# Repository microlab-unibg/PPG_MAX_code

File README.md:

# IoT_Sensor

This GitHub project contains a library for configuring registers and reading data from the MAX86916 sensor to calculate heart rate (HR) using a peak detection algorithm. The MAX86916 is a highly integrated optical sensor module that can be used for pulse oximetry and heart rate monitoring. The library provided in this project simplifies the process of interfacing with the sensor and extracting the HR information using an efficient peak detection algorithm. The library can be easily integrated into an existing codebase, and the project also includes sample code to demonstrate the usage of the library.

## HR-Calculation

### Begin()
- Starts I2C communication between Arduino and sensor by calling the Wire.begin() function.
- Sets the clock speed for the I2C communication to I2C_SPEED_FAST using the Wire.setClock() function.
- Calls the read_Part_ID() function to read the part ID from the MAX86916 sensor.
- Compares the part ID read from the sensor to the expected part ID (MAX86916_EXPECTED_PART_ID).
- If the part ID does not match the expected part ID, the function returns false, indicating an error.
- Calls the read_Revision_ID() function to read the revision ID from the MAX86916 sensor.
- If everything is working correctly, the function returns true.
### Setup()
- Calls the softReset() function to reset the sensor.
- Configures the FIFO (First In First Out) buffer by calling the setFIFOAverage() function to set the sample average, and the enableFIFORollover() function to allow the FIFO to roll over.
- Configures the LED mode by calling the setLEDMode() function with the specified ledMode parameter. The activeLEDs variable is set based on the ledMode parameter.
- Configures the particle sensing by calling the setADCRange(), setSampleRate(), and setPulseWidth() functions with the specified parameters.
- Configures the LED pulse amplitude by calling the setAllLEDRange() function with the specified range parameter, and the setPA_IR(), setPA_RED(), setPA_GREEN(), setPA_BLUE(), and setPA_PROX() functions with the specified powerLevel parameter.
- Configures the Flex-LED mode by calling the enableSlot() function to enable the reading of the LEDs, depending on the ledMode parameter.
- Calls the clearFIFO() function to reset the FIFO buffer.
### Read FIFO()
- The function returns a 16-bit unsigned integer that represents the number of new data samples that were read from the sensor.
- The function first reads the read and write pointers of the FIFO register to determine how much new data is available.
- If there is new data available, the function calculates the number of samples to read and the number of bytes to request from the sensor.
- The function then enters a loop where it repeatedly requests blocks of data from the sensor and stores the data in the buffer.
- Within the loop, the function reads three bytes at a time and converts them to 32-bit unsigned integers.
- The function then applies a bit mask to zero out all but the 18 least significant bits of the integer, which are the meaningful data bits.
- Finally, the function stores the converted integer values in the appropriate arrays within the buffer.
### Get Current value()
This function is a method of a MAX86916 class that retrieves the most recent Green value from the sensor data buffer. It first calls the safeCheck() function, which checks the sensor for new data for 250ms and returns a boolean indicating whether new data was found. If new data is found, it returns the most recent Green value from the sensor_data_buffer array by accessing the array element at the current head index. If no new data is found, it returns 0 to indicate that the sensor failed to find new data. This function assumes that the sensor data buffer has been properly initialized and that the head index has been properly updated by the readFIFO() function.
### Apply lowpassfilter()
This function applies a first-order low-pass filter to the input signal using the one-pole recursive filter algorithm. The filter is implemented using a lowpassFilter1p struct that contains the previous input value and the filter coefficient (pt1K).
The function then updates the previous input value to the current output value for the next iteration of the filter.
Finally, the function returns the filtered output signal.
### Apply removeDC()
This function applies a DC removal filter to the input signal using a first-order high-pass filter with the given alpha coefficient. The function takes three parameters: the input signal to be filtered (x), the previous filtered value (prev_w), and the alpha coefficient (alpha) that determines the amount of filtering.
The function creates a DigitalFilter::dcFilter_t struct to hold the filtered and intermediate values, and returns the filtered value at the end.
### Apply medianfilter()
This function applies a mean difference filter to the input signal using a sliding window of a specified size. The function takes two parameters: the input signal to be filtered (M), and a pointer to the meanDiffFilter_t struct (filterValues) containing the filter parameters.
The function calculates the filtered output signal as the difference between the input signal and the moving average of the window. The filter parameters include an array of values (values), the sum of the values (sum), the index of the current position in the sliding window (index), and the count of values in the sliding window (count).
The function first subtracts the oldest value in the sliding window from the sum. It then inserts the new value at the current index and adds it to the sum. The index is then moved to the next position in the sliding window. If the sliding window is not full, the count of values in the window is increased.
The function calculates the moving average of the window by dividing the sum by the count. It then returns the difference between the moving average and the input signal.
### Apply butterworthfilter()
This function applies a fourth-order low-pass filter to the input signal using pre-calculated filter coefficients. The coefficients were calculated in Matlab based on some samples of the input signal.
The filter has four zeros (NZEROS) and four poles (NPOLES), and a gain factor (GAIN) of 3.775352055e+02.
The function uses two arrays, xv and yv, to maintain a history of the input and output values, respectively. The input value x is first scaled by the pre-calculated gain and then inserted into the input history buffer.
The output history buffer is shifted, and the new output value is calculated using the pre-calculated filter coefficients and the history buffer values. The function returns the new output value.
Note that the filter coefficients and the gain factor were pre-calculated in Matlab and are hardcoded in the function.
### Peak detection algorithm
After the signal was filtered, the next step was to apply the peak detection algorithm to the filtered signal. This algorithm identified the peaks in the signal, which corresponded to the heartbeats.
### Calculate HR
For each peak found, the time between the different peaks was calculated to determine the heart rate

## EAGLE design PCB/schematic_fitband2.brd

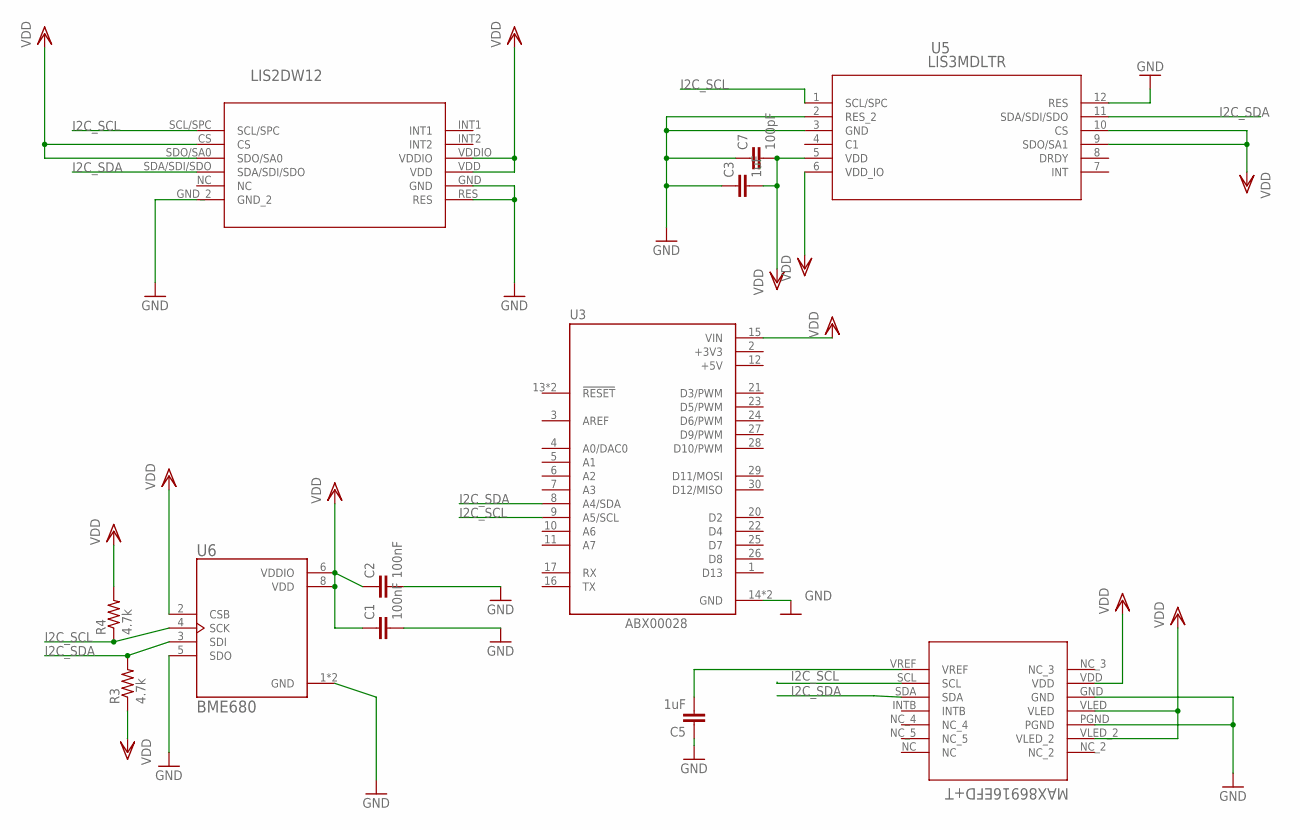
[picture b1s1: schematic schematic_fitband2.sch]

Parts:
C1, C2: 100nF; 221E_PASSIVES_C0402
C3, C5: 1uF; 221E_PASSIVES_C0402
C7: 100pF; 221E_PASSIVES_C0402
R3, R4: 4.7k; M0805
U1: MAX86916EFD+T; 21-100325_90-100122
U2: LIS2DW12; LIS2DW12_LGA-12_2X2X0P7_STM
U3: ABX00028; MODULE_ABX00028
U5: LIS3MDLTR; LGA-12_2X2X1_STM
U6: BME680; PSON80P300X300X100-8N

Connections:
+3V3: U3.2 (+3V3)
+5V: U3.12 (+5V)
GND: C1.P$2 (2), C2.P$2 (2), C3.P$1 (1), C5.P$1 (1), C7.P$1 (1), U1.GND, U1.PGND, U2.GND, U2.GND_2, U2.RES, U3.14 (GND), U3.19 (GND), U5.2 (RES_2), U5.3 (GND), U5.12 (RES), U6.1 (GND), U6.5 (SDO), U6.7 (GND)
I2C_SCL: R4.1, U1.SCL, U2.SCL/SPC, U3.9 (A5/SCL), U5.1 (SCL/SPC), U6.4 (SCK)
I2C_SDA: R3.2, U1.SDA, U2.SDA/SDI/SDO, U3.8 (A4/SDA), U5.11 (SDA/SDI/SDO), U6.3 (SDI)
unnamed: C5.P$2 (2), U1.VREF
VDD: C1.P$1 (1), C2.P$1 (1), C3.P$2 (2), C7.P$2 (2), R3.1, R4.2, U1.VDD, U1.VLED, U1.VLED_2, U2.CS, U2.SDO/SA0, U2.VDD, U2.VDDIO, U3.15 (VIN), U5.5 (VDD), U5.6 (VDD_IO), U5.9 (SDO/SA1), U5.10 (CS), U6.2 (CSB), U6.6 (VDDIO), U6.8 (VDD)

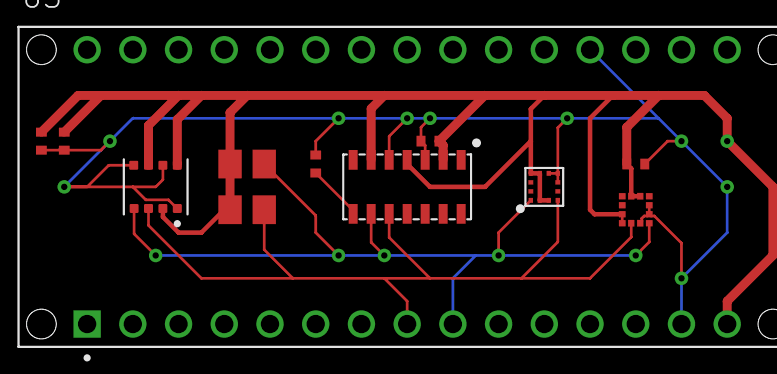
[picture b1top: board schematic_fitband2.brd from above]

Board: 2 copper layers, 12 parts (0 on the bottom side), 5 nets.

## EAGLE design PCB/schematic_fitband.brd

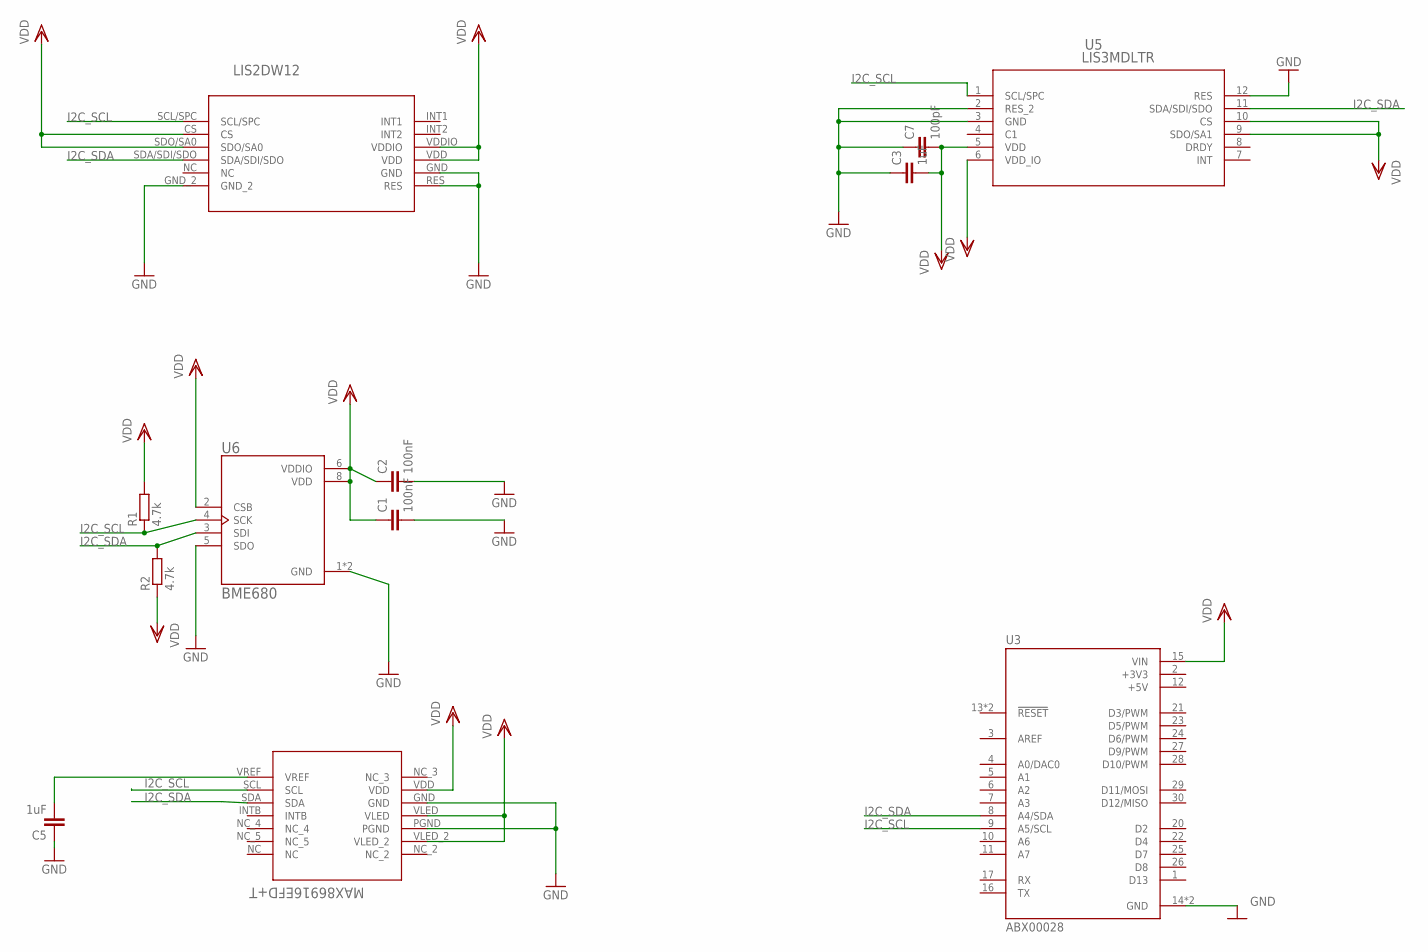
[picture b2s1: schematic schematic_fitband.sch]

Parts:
C1, C2: 100nF; 221E_PASSIVES_C0402
C3, C5: 1uF; 221E_PASSIVES_C0402
C7: 100pF; 221E_PASSIVES_C0402
R1, R2: 4.7k; MINI_MELF-0204R
U1: MAX86916EFD+T; 21-100325_90-100122
U2: LIS2DW12; LIS2DW12_LGA-12_2X2X0P7_STM
U3: ABX00028; MODULE_ABX00028
U5: LIS3MDLTR; LGA-12_2X2X1_STM
U6: BME680; PSON80P300X300X100-8N

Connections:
+3V3: U3.2 (+3V3)
+5V: U3.12 (+5V)
GND: C1.P$2 (2), C2.P$2 (2), C3.P$1 (1), C5.P$1 (1), C7.P$1 (1), U1.GND, U1.PGND, U2.GND, U2.GND_2, U2.RES, U3.14 (GND), U3.19 (GND), U5.2 (RES_2), U5.3 (GND), U5.12 (RES), U6.1 (GND), U6.5 (SDO), U6.7 (GND)
I2C_SCL: R1.1, U1.SCL, U2.SCL/SPC, U3.9 (A5/SCL), U5.1 (SCL/SPC), U6.4 (SCK)
I2C_SDA: R2.2, U1.SDA, U2.SDA/SDI/SDO, U3.8 (A4/SDA), U5.11 (SDA/SDI/SDO), U6.3 (SDI)
unnamed: C5.P$2 (2), U1.VREF
unnamed: R1.2, U6.2 (CSB)
VDD: C1.P$1 (1), C2.P$1 (1), C3.P$2 (2), C7.P$2 (2), R2.1, U1.VDD, U1.VLED, U1.VLED_2, U2.CS, U2.SDO/SA0, U2.VDD, U2.VDDIO, U3.15 (VIN), U5.5 (VDD), U5.6 (VDD_IO), U5.9 (SDO/SA1), U5.10 (CS), U6.6 (VDDIO), U6.8 (VDD)

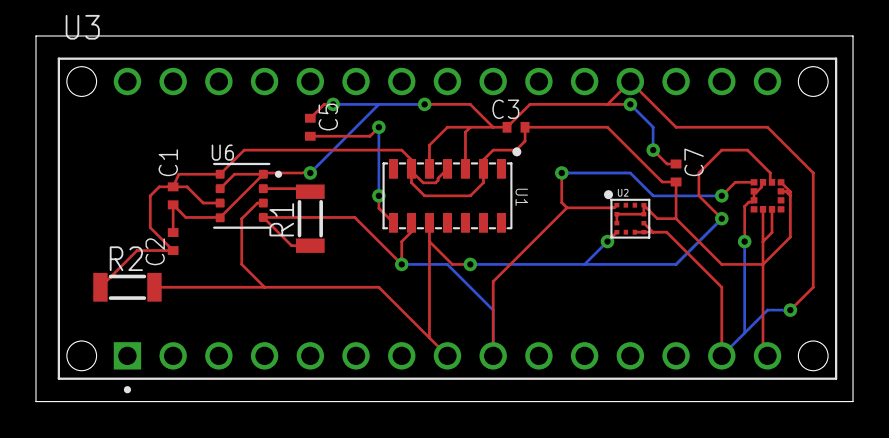
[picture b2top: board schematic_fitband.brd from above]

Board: 2 copper layers, 45.4 x 20.3 mm, 12 parts (0 on the bottom side), 6 nets.

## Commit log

2023-02-10 Configuration classes
2023-02-13 PPG configuration
2023-02-13 led_current configuration
2023-02-20 led_sequence configuration+ fifo configuration
2023-02-21 small changes
2023-03-12 MAX8691 class
2023-03-13 Create Use
2023-04-16 project structure
2023-04-18 electronics
2023-12-18 FIX - Missing declarations in cmFilter.cpp and file structure
2023-12-20 FIX - GAIN didnt have space godd****

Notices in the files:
parts and their libraries:
COPYRIGHT: Copyright (C) 2018 Accelerated Designs. All rights reserved
COPYRIGHT: Copyright (C) 2023 Ultra Librarian. All rights reserved.
